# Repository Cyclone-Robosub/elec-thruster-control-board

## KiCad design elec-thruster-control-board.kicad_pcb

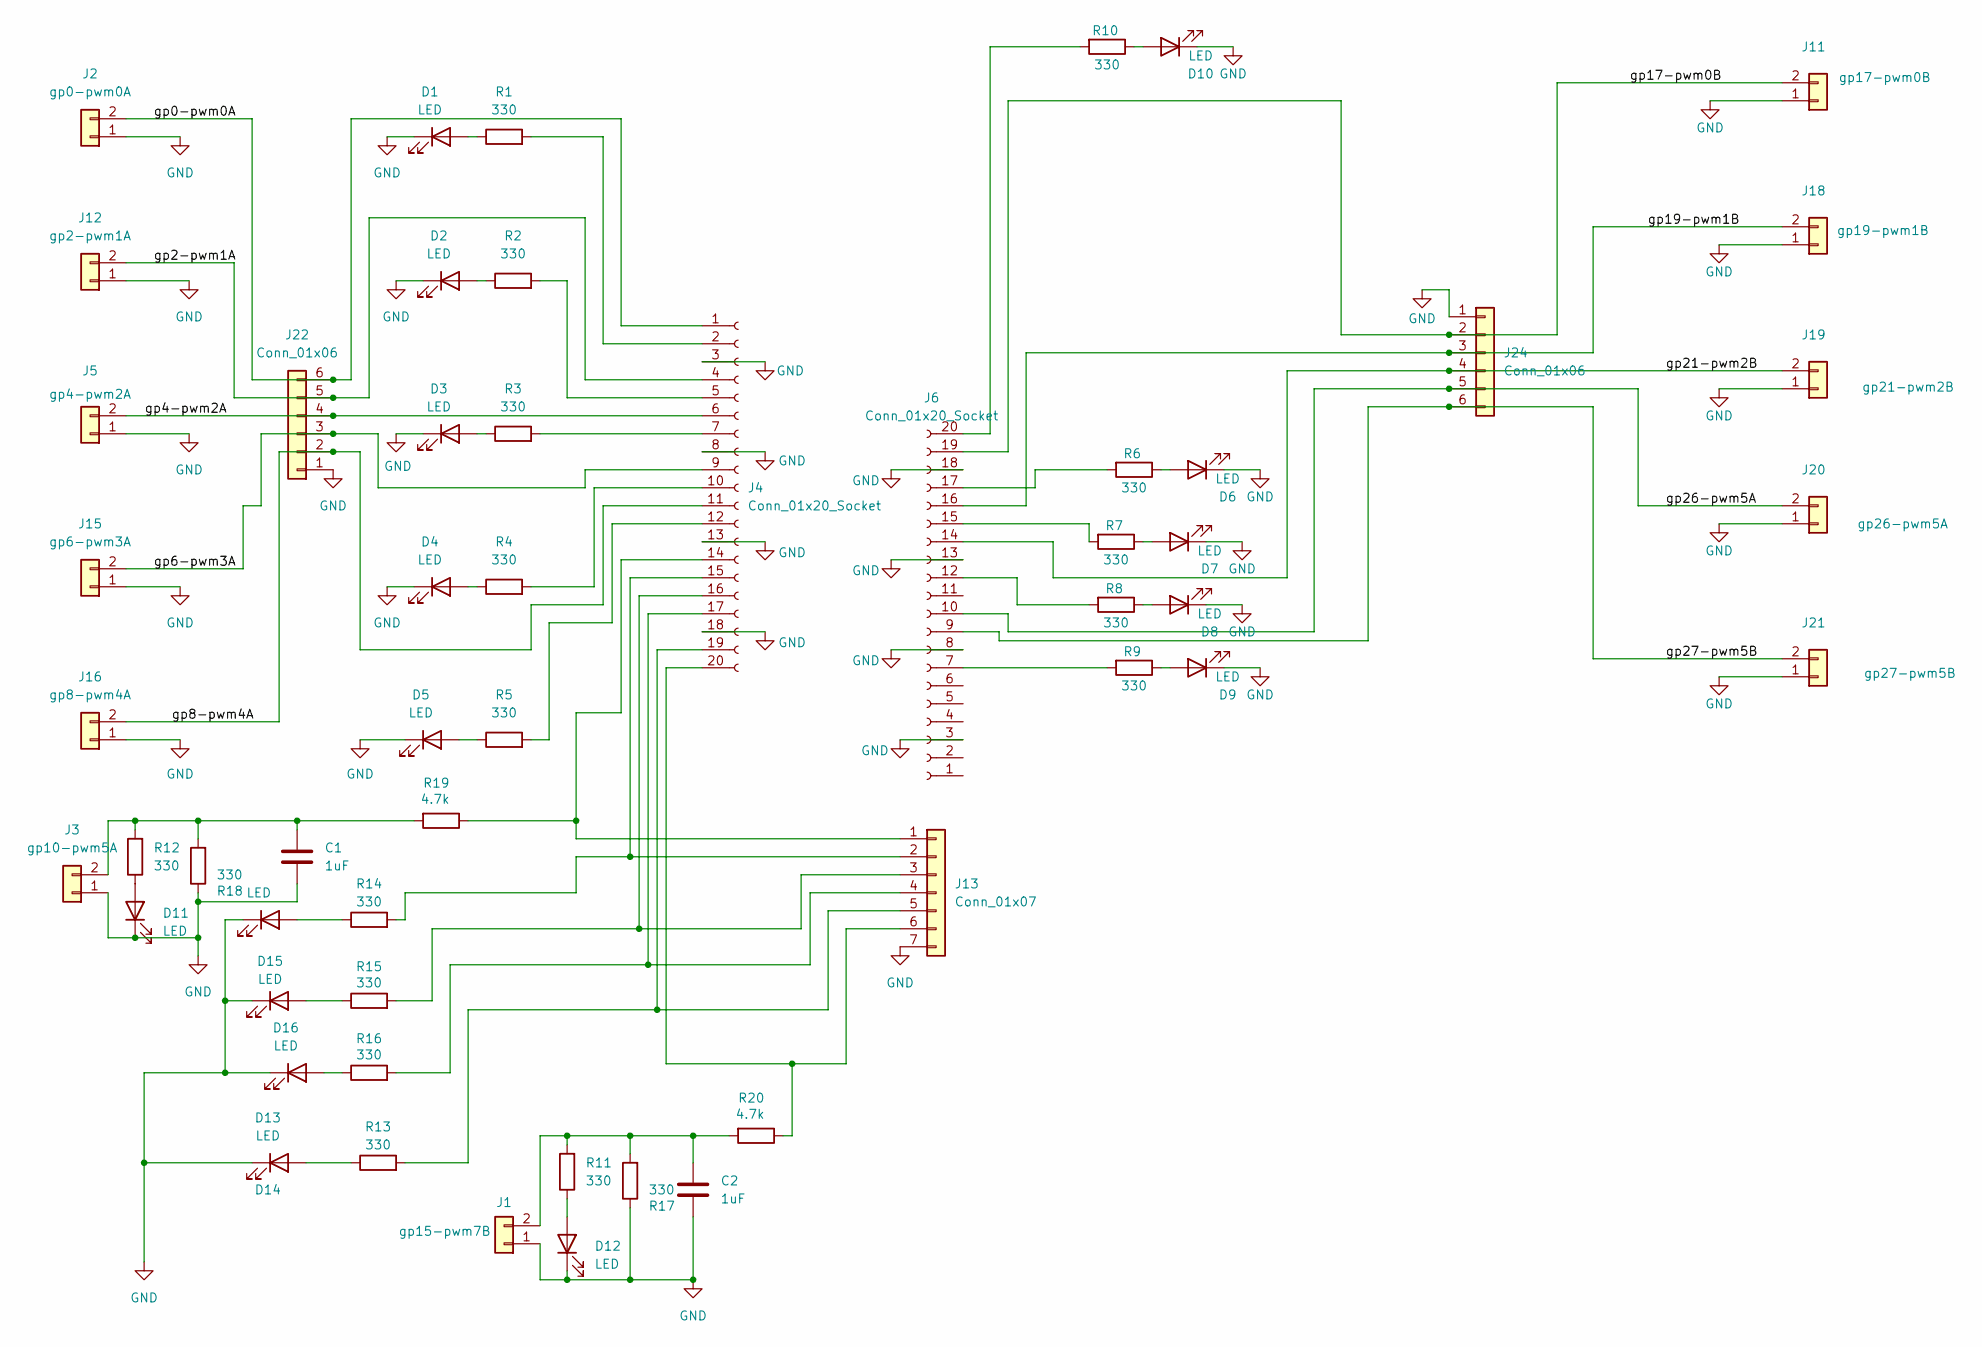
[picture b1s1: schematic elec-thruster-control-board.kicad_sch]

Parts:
C1, C2: 1uF; C_0805_2012Metric
D1, D2, D3, D4, D5, D6, D7, D8, D9, D10, D11, D12, D13, D14, D15, D16: LED; LED_APT2012LZGCK
J1: gp15-pwm7B; JST_PH_B2B-PH-K_1x02_P2.00mm_Vertical
J2: gp0-pwm0A; JST_PH_B2B-PH-K_1x02_P2.00mm_Vertical
J3: gp10-pwm5A; JST_PH_B2B-PH-K_1x02_P2.00mm_Vertical
J4, J6: Conn_01x20_Socket; PinSocket_1x20_P2.54mm_Vertical
J5: gp4-pwm2A; JST_PH_B2B-PH-K_1x02_P2.00mm_Vertical
J11: gp17-pwm0B; JST_PH_B2B-PH-K_1x02_P2.00mm_Vertical
J12: gp2-pwm1A; JST_PH_B2B-PH-K_1x02_P2.00mm_Vertical
J13: Conn_01x07; PinHeader_1x07_P2.54mm_Vertical
J15: gp6-pwm3A; JST_PH_B2B-PH-K_1x02_P2.00mm_Vertical
J16: gp8-pwm4A; JST_PH_B2B-PH-K_1x02_P2.00mm_Vertical
J18: gp19-pwm1B; JST_PH_B2B-PH-K_1x02_P2.00mm_Vertical
J19: gp21-pwm2B; JST_PH_B2B-PH-K_1x02_P2.00mm_Vertical
J20: gp26-pwm5A; JST_PH_B2B-PH-K_1x02_P2.00mm_Vertical
J21: gp27-pwm5B; JST_PH_B2B-PH-K_1x02_P2.00mm_Vertical
J22, J24: Conn_01x06; PinHeader_1x06_P2.54mm_Vertical
R1, R2, R3, R4, R5, R6, R7, R8, R9, R10, R11, R12, R13, R14, R15, R16, R17, R18: 330; RESC2012X65N
R19, R20: 4.7k; RESC2012X65N

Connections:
/gp0-pwm0A: J2.2, J4.1, J22.6
/gp2-pwm1A: J4.4, J12.2, J22.5
/gp4-pwm2A: J4.6, J5.2, J22.4
/gp6-pwm3A: J4.9, J15.2, J22.3
/gp8-pwm4A: J4.11, J16.2, J22.2
/gp17-pwm0B: J6.19, J11.2, J24.2
/gp19-pwm1B: J6.16, J18.2, J24.3
/gp21-pwm2B: J6.14, J19.2, J24.4
/gp26-pwm5A: J6.10, J20.2, J24.5
/gp27-pwm5B: J6.9, J21.2, J24.6
GND: C1.2, C2.2, D1.1 (K), D2.1 (K), D3.1 (K), D4.1 (K), D5.1 (K), D6.1 (K), D7.1 (K), D8.1 (K), D9.1 (K), D10.1 (K), D11.1 (K), D12.1 (K), D13.1 (K), D14.1 (K), D15.1 (K), D16.1 (K), J1.1, J2.1, J3.1, J4.3, J4.8, J4.13, J4.18, J5.1, J6.3, J6.8, J6.13, J6.18, J11.1, J12.1, J13.7, J15.1, J16.1, J18.1, J19.1, J20.1, J21.1, J22.1, J24.1, R17.1, R18.1
unnamed: D1.2 (A), R1.1
unnamed: D2.2 (A), R2.1
unnamed: D3.2 (A), R3.1
unnamed: D4.2 (A), R4.1
unnamed: D5.2 (A), R5.1
unnamed: D6.2 (A), R6.1
unnamed: D7.2 (A), R7.1
unnamed: D8.2 (A), R8.1
unnamed: D9.2 (A), R9.1
unnamed: D10.2 (A), R10.1
unnamed: D11.2 (A), R12.1
unnamed: D12.2 (A), R11.1
unnamed: D13.2 (A), R13.1
unnamed: D14.2 (A), R14.1
unnamed: D15.2 (A), R15.1
unnamed: D16.2 (A), R16.1
unnamed: C2.1, J1.2, R11.2, R17.2, R20.2
unnamed: C1.1, J3.2, R12.2, R18.2, R19.2
unnamed: J4.2, R1.2
unnamed: J4.5, R2.2
unnamed: J4.7, R3.2
unnamed: J4.10, R4.2
unnamed: J4.12, R5.2
unnamed: J6.7, R9.2
unnamed: J6.12, R8.2
unnamed: J6.15, R7.2
unnamed: J6.17, R6.2
unnamed: J6.20, R10.2
unnamed: J4.14, J13.1, R19.1
unnamed: J4.15, J13.2, R14.2
unnamed: J4.16, J13.3, R15.2
unnamed: J4.17, J13.4, R16.2
unnamed: J4.19, J13.5, R13.2
unnamed: J4.20, J13.6, R20.1

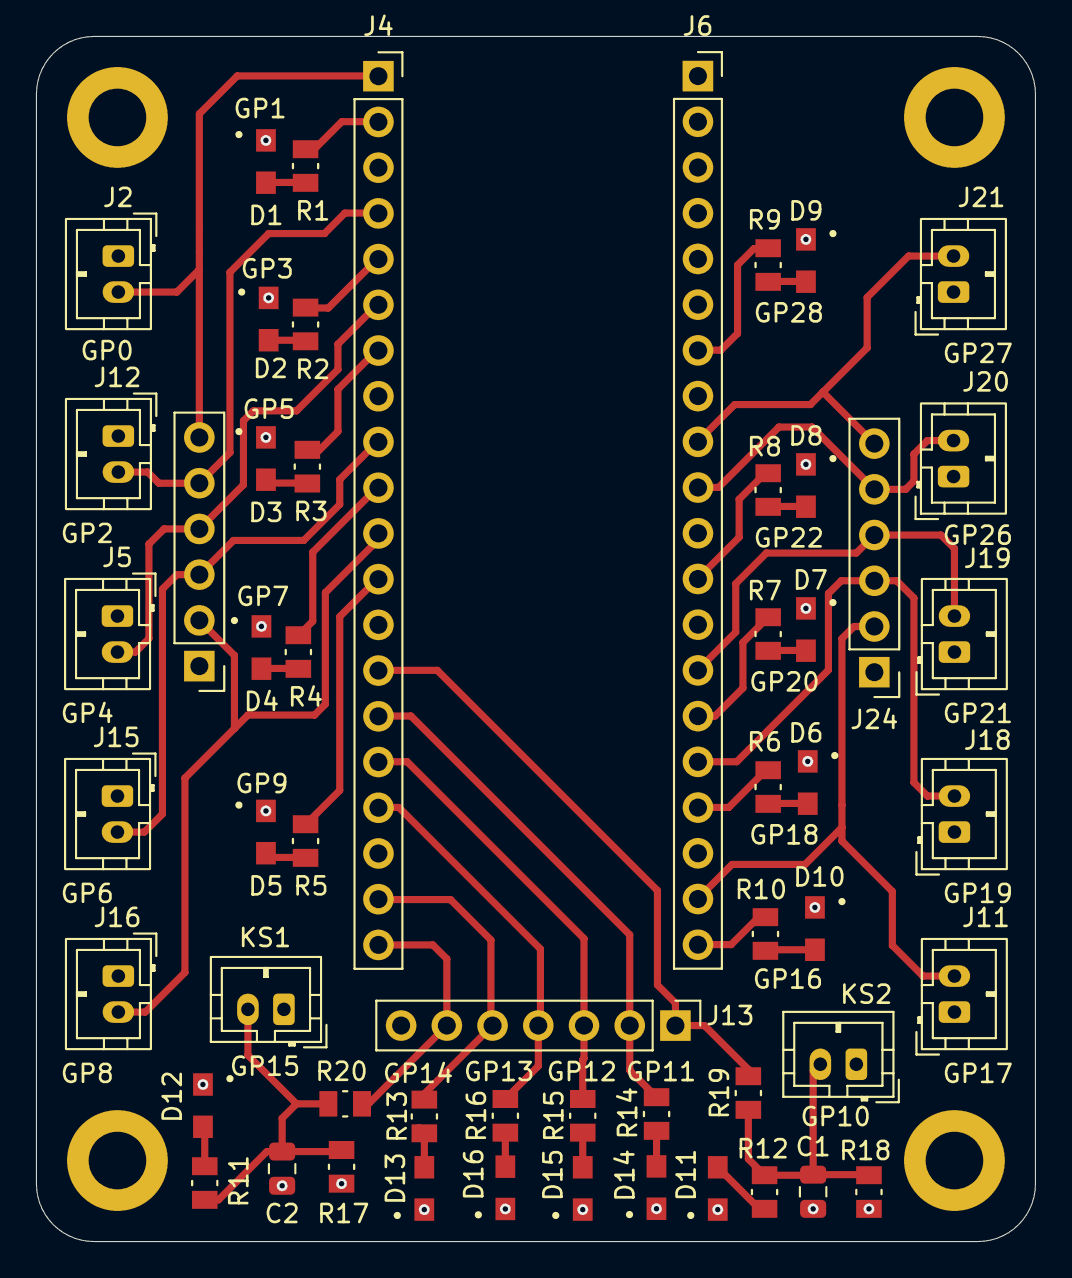
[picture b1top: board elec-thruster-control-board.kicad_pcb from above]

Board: 2 copper layers, 55.5 x 67.0 mm, 59 parts (0 on the bottom side), 45 nets.

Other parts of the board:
H1, H2, H3, H4: MountingHole; MountingHole_3.2mm_M3_DIN965_Pad

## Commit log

2026-01-10 project setup
2026-01-10 Added Kekoa and Marco's work from Google Drive
2026-01-11 Update 4:25 rewired to fit a pico footprint
2026-01-11 I fixed it such that the board now accurately fits a Pi Pico
2026-01-13 needs work on the traces
2026-01-17 Removed overlap of labels, added single test connectors next to each pwm, fixed breakout header to fit with 8input logic analyzer
2026-01-17 hi this is the work I did thursday
    This is the work I did on Thursday.
2026-01-17 Removed extra LED overlap, redid wiring to separate connectors connected to identical pwm channels, labeled pwm channels
2026-01-17 fixed labels
2026-01-25 Add files via upload
    Major MAJOR changes to everything. Added variable wire thicknesses and fixed a lot of things.
2026-01-25 Made many changes to wire thickness and many fixes
2026-01-27 Updated design
2026-01-27 45 angle
2026-01-27 fixed drc errors
2026-01-27 This is based on a modified version of Dilraj's circuit.
2026-01-30 Painstakingly added better silkscreening and MOUNTING HOLES!
2026-01-31 Broke out PWMs through 5 pin connectors
2026-02-01 Updated footprint to vertical JST Connector for PCB and Schematic Please enter the commit message for your changes. Lines starting
2026-02-01 Forgot to push PCB update. Now addded updated PCB with vertical JST connectors
2026-02-03 Added 1x6 connectors to breakout PWMs (including a pin for ground), and a 1x7 connector for the LEDs (also with pin for ground)
2026-02-03 Added footprints for breakout 1x6 and 1x7 connectors
2026-02-03 Fixed connector footprint + Orientation on right side
2026-02-03 Modified PCB layout to accomodate for connectors (unfinished)
2026-02-03 Deleted one pin headers
2026-02-03 Nearly finalized design here.
2026-02-03 Oops made a small mistake
2026-02-10 branch worked on by Kekoa to space out the connectors and clean up routing
2026-02-10 This is the true final edition of this project
2026-02-10 Updated footprints in the schematic and pcb design. Also cleaned up some of the routing.
2026-02-14 Final PCB Design after design review Updated dimensions of board and mounting hole distance Fixed LED footprint Added Measurement values
2026-02-14 Added Labels for LEDs, and corrected Labels
2026-02-14 Minor fix
2026-02-14 Moved left LEDs closer to pico
2026-02-15 Tightened spacing on both side of board should save ~6.5mm in width if 5mm gap between header and connector. Can save ~10.5mm if 3mm gap between header and connector. Wire connection still incomplete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
2026-02-20 Finished the job for Kekoa's compression
2026-02-20 I finished the compression
2026-02-20 just double checking
2026-02-22 Added Kill switch connectors and LEDs to schematic Made minor fixes to pcb design
2026-02-24 Added the killswitch connectors pulldowns + LED. FIX THE FOOTPRINT ISSUES IN PCB MODE
2026-02-24 This is a branch of the tighter space configuration now. Killswitch circuitry is now added. FIX THE FOOTPRINTING ISSUES
2026-02-27 Almost done just need to modify the LEDs
2026-02-28 Condensed Board and Finalized KS LED and Resistor
2026-02-28 Condensed board and finalized KS LEDs and resistors
2026-02-28 Updated Schematic
2026-04-04 The definitive final edition of our thruster control board.
2026-04-04 Ok I think we are finalized now
2026-04-07 Deleted unncessary labels for mounting holes & kill switch
2026-04-07 Work in progress for the final design revision
2026-04-10 Made several changes to the board. Almost done just needs RC
2026-04-17 Ok heres the final final final final version mkay
2026-04-21 Added Capacitor Values. Started BOM
2026-05-02 Completed BOM (and updated connector and resistors values to be correct)
2026-05-05 Final Draft of the Board (Hopefully Finalized) Updated all footprints to match parts in BOM Moved reference designators to proper locations (as importing new footprints moved them) Moved Kill switch 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
2026-05-05 Ran DRC and fixed errors
2026-05-05 Cleaned up trace spacing
2026-05-05 Added Assembly Notes to board (Listed under the user comments layer)
2026-05-10 Fixed some spacing and added Gerber files
2026-06-30 Fixed resistor values
